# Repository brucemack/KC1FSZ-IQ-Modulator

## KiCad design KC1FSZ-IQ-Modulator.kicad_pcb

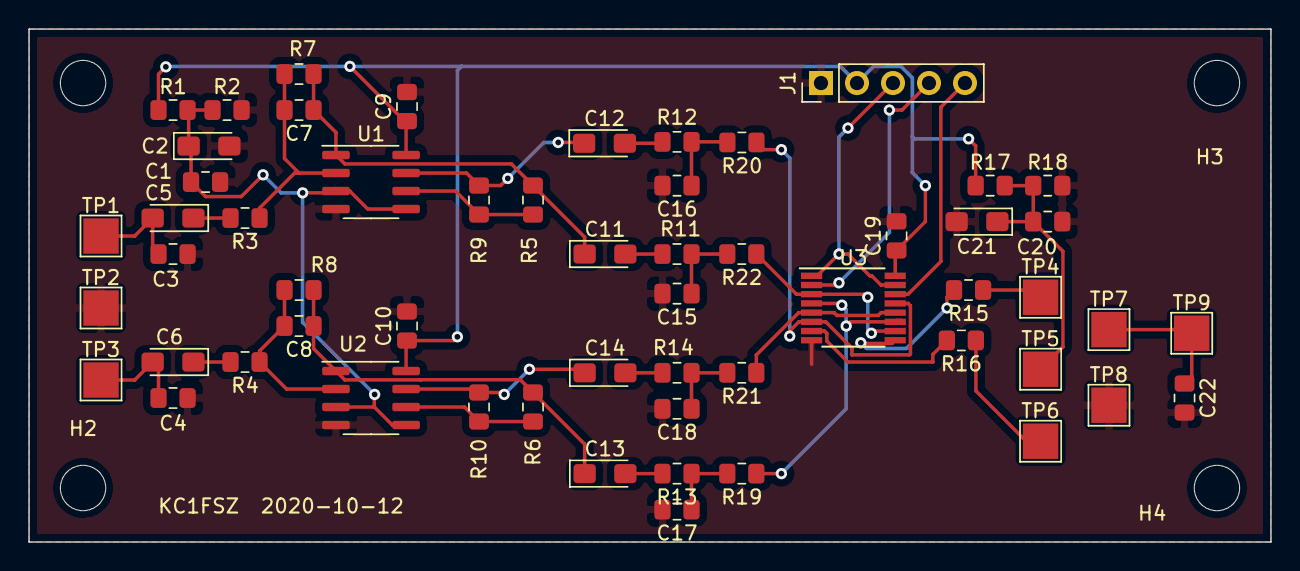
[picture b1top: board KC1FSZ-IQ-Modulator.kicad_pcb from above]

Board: 2 copper layers, 87.6 x 36.2 mm, 61 parts (0 on the bottom side), 36 nets.

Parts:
C1, C3, C4, C7, C8, C9, C10, C15, C16, C17, C18, C19, C20, C22: C; C_0805_2012Metric_Pad1.15x1.40mm_HandSolder
C2: CP; CP_EIA-3216-18_Kemet-A_Pad1.58x1.35mm_HandSolder
C5, C6, C11, C12, C13, C14, C21: CP; CP_EIA-3216-10_Kemet-I_Pad1.58x1.35mm_HandSolder
H1, H2, H3, H4: MountingHole; MountingHole_3.2mm_M3
J1: Conn_01x05_Male; PinHeader_1x05_P2.54mm_Vertical
R1, R2, R3, R4, R5, R6, R7, R8, R9, R10, R11, R12, R13, R14, R17, R18: R; R_0805_2012Metric_Pad1.15x1.40mm_HandSolder
R15, R16: 49.9; R_0805_2012Metric_Pad1.15x1.40mm_HandSolder
R19, R20, R21, R22: 0; R_0805_2012Metric_Pad1.15x1.40mm_HandSolder
TP1, TP2, TP3, TP4, TP5, TP6, TP7, TP8, TP9: TestPoint; TestPoint_Pad_2.5x2.5mm
U1, U2: TLV2462CD; SOIC-8_3.9x4.9mm_P1.27mm
U3: SN74CBT3253; TSSOP-16_4.4x5mm_P0.65mm

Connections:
+5V: C9.1, C10.1, C19.1, J1.2, R1.1, R17.1, U1.8, U2.8, U3.16
CLK0: J1.4, U3.2
CLK1: J1.5, U3.14
GND: C1.2, C2.2, C3.2, C4.2, C9.2, C10.2, C15.2, C16.2, C17.2, C18.2, C19.2, C20.2, C21.2, C22.2, J1.1, R2.2, R18.2, TP2.1, TP8.1, U1.4, U2.4, U3.8
unnamed: C3.1, C5.2, TP1.1
unnamed: C4.1, C6.2, TP3.1
unnamed: C5.1, R3.2
unnamed: C6.1, R4.2
unnamed: C7.2, R3.1, R7.2, U1.2
unnamed: C8.2, R4.1, R8.2, U2.2
unnamed: C7.1, C11.1, R5.2, R7.1, U1.1
unnamed: C11.2, R11.2
unnamed: C12.1, R9.1, U1.7
unnamed: C12.2, R12.2
unnamed: C8.1, C13.1, R6.2, R8.1, U2.1
unnamed: C13.2, R13.2
unnamed: C14.1, R10.1, U2.7
unnamed: C14.2, R14.2
unnamed: C15.1, R11.1, R22.2
unnamed: C16.1, R12.1, R20.2
unnamed: C17.1, R13.1, R19.2
unnamed: C18.1, R14.1, R21.2
unnamed: C20.1, C21.1, R17.2, R18.1, TP5.1
unnamed: C22.1, TP7.1, TP9.1
unnamed: R5.1, R9.2, U1.6
unnamed: R6.1, R10.2, U2.6
unnamed: R15.1, TP4.1
unnamed: R15.2, U3.9
unnamed: R16.1, TP6.1
unnamed: R16.2, U3.7
unnamed: R19.1, U3.4, U3.11
unnamed: R20.1, U3.6, U3.13
unnamed: R21.1, U3.5, U3.12
unnamed: R22.1, U3.3, U3.10
VMID: C1.1, C2.1, R1.2, R2.1, U1.3, U1.5, U2.3, U2.5
~EN: J1.3, U3.1, U3.15
